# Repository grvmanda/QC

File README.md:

# QC

Attempt at making an all custom hardware quadcop to serve as a platform to test control algorithms

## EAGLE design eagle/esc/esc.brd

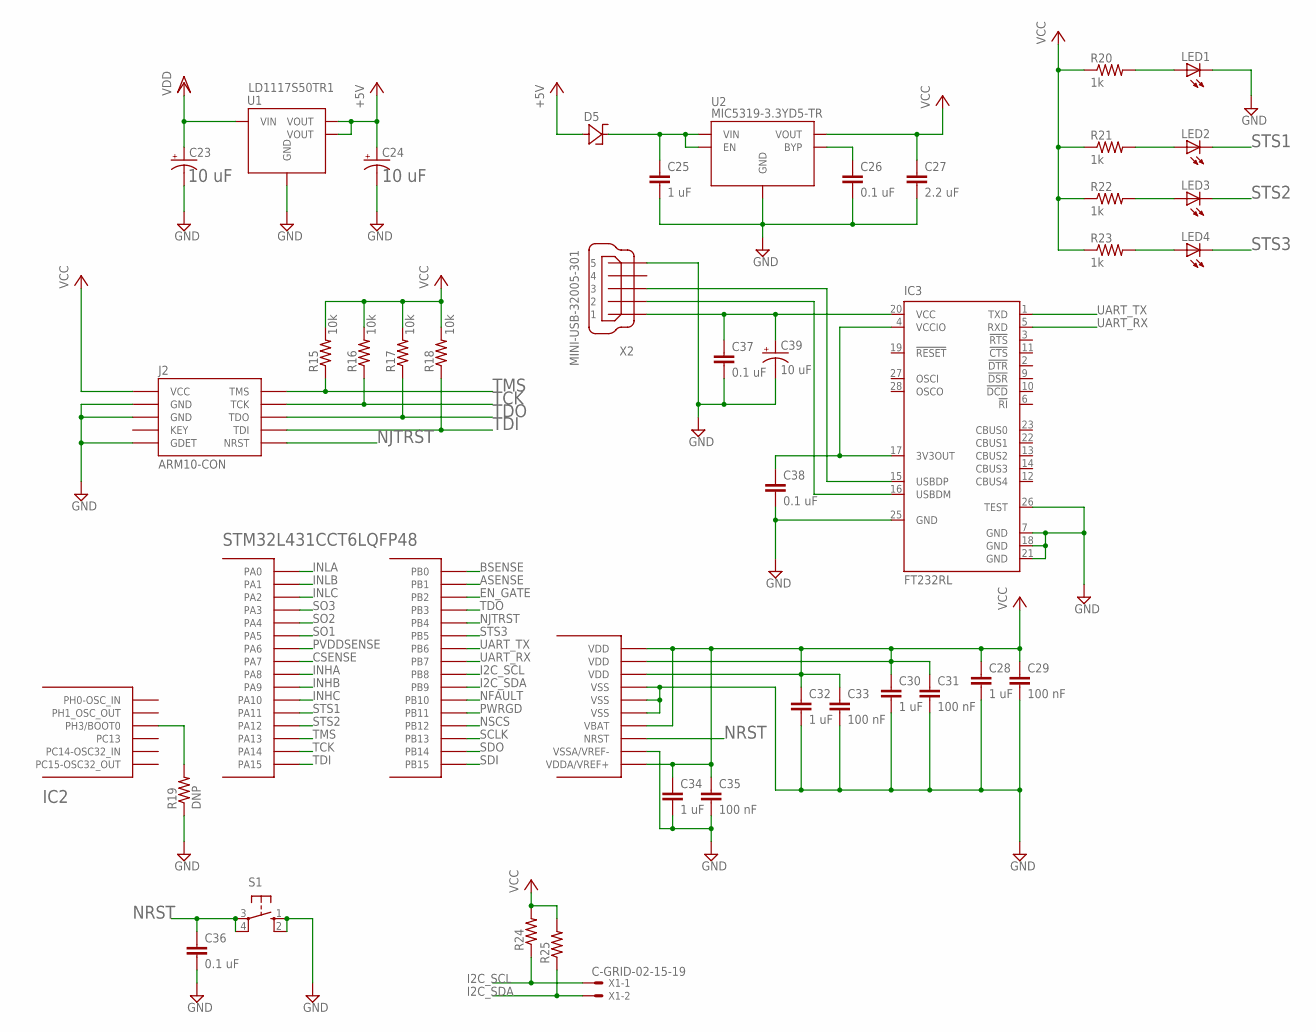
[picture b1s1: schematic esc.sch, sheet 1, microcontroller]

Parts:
C23: 10 uF; CAPAE430X580N
C24: CAPACITOR4.3X4.3; CAPAE430X580N
C25, C28, C30, C32, C34: 1 uF; C0603
C26, C36, C37, C38: 0.1 uF; C0603
C27: 2.2 uF; C0603
C29, C31, C33, C35: 100 nF; C0603
C39: 10 uF; CT3216
D5: STPS2L30ASMA; DIOM5025X245N
IC2: STM32L431CCT6LQFP48; QFP50P900X900X160-48N
IC3: FT232RL; SSOP28
J2: ARM10-CON; 10-PIN-1.27-PITCH
LED1, LED2, LED3, LED4: LED_ESML0603; LED_SML0603
R15, R16, R17, R18: 10k; R0603
R19: DNP; R0603
R20, R21, R22, R23: 1k; R0603
R24, R25: R-US_R0603; R0603
S1: 10-XX; B3F-10XX
U1: LD1117S50TR1; SOT230P700X180-4N
U2: MIC5319-3.3YD5-TR; SOT95P290X110-5N
X1: C-GRID-02-15-19; 15-91-02
X2: MINI-USB-32005-301; 32005-301

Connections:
+5V: C24.1 (+), D5.2 (A), U1.2 (VOUT), U1.4 (VOUT)
ASENSE: IC2.19 (PB1); also elsewhere on the board
BSENSE: IC2.18 (PB0); also elsewhere on the board
CSENSE: IC2.17 (PA7); also elsewhere on the board
EN_GATE: IC2.20 (PB2); also elsewhere on the board
GND: C23.2 (-), C24.2 (-), C25.2, C26.2, C27.2, C28.2, C29.2, C30.2, C31.2, C32.2, C33.2, C34.2, C35.2, C36.2, C37.2, C38.2, C39.+ (-), IC2.8 (VSSA/VREF-), IC2.23 (VSS), IC2.35 (VSS), IC2.47 (VSS), IC3.7 (GND), IC3.18 (GND), IC3.21 (GND), IC3.25 (GND), IC3.26 (TEST), J2.3 (GND), J2.5 (GND), J2.9 (GDET), LED1.C, R19.1, S1.1 (S), S1.2 (S1), U1.1 (GND), U2.2 (GND), X2.5; also elsewhere on the board
I2C_SCL: IC2.45 (PB8), R24.1, X1.1
I2C_SDA: IC2.46 (PB9), R25.1, X1.2
INHA: IC2.29 (PA8); also elsewhere on the board
INHB: IC2.30 (PA9); also elsewhere on the board
INHC: IC2.31 (PA10); also elsewhere on the board
INLA: IC2.10 (PA0); also elsewhere on the board
INLB: IC2.11 (PA1); also elsewhere on the board
INLC: IC2.12 (PA2); also elsewhere on the board
unnamed: C25.1, D5.1 (C), U2.1 (VIN), U2.3 (EN)
unnamed: C26.1, U2.4 (BYP)
unnamed: IC2.44 (PH3/BOOT0), R19.2
unnamed: LED1.A, R20.2
unnamed: C37.1, C39.- (+), IC3.20 (VCC), X2.1
unnamed: LED2.A, R21.2
unnamed: LED3.A, R22.2
unnamed: LED4.A, R23.2
unnamed: C38.1, IC3.4 (VCCIO), IC3.17 (3V3OUT)
unnamed: IC3.16 (USBDM), X2.2
unnamed: IC3.15 (USBDP), X2.3
NFAULT: IC2.21 (PB10); also elsewhere on the board
NJTRST: IC2.40 (PB4), J2.10 (NRST)
NRST: C36.1, IC2.7 (NRST), S1.3, S1.4 (P1)
NSCS: IC2.25 (PB12); also elsewhere on the board
PVDDSENSE: IC2.16 (PA6); also elsewhere on the board
PWRGD: IC2.22 (PB11); also elsewhere on the board
SCLK: IC2.26 (PB13); also elsewhere on the board
SDI: IC2.28 (PB15); also elsewhere on the board
SDO: IC2.27 (PB14); also elsewhere on the board
SO1: IC2.15 (PA5); also elsewhere on the board
SO2: IC2.14 (PA4); also elsewhere on the board
SO3: IC2.13 (PA3); also elsewhere on the board
STS1: IC2.32 (PA11), LED2.C
STS2: IC2.33 (PA12), LED3.C
STS3: IC2.41 (PB5), LED4.C
TCK: IC2.37 (PA14), J2.4 (TCK), R16.1
TDI: IC2.38 (PA15), J2.8 (TDI), R18.1
TDO: IC2.39 (PB3), J2.6 (TDO), R17.1
TMS: IC2.34 (PA13), J2.2 (TMS), R15.1
UART_RX: IC2.43 (PB7), IC3.5 (RXD)
UART_TX: IC2.42 (PB6), IC3.1 (TXD)
VCC: C27.1, C28.1, C29.1, C30.1, C31.1, C32.1, C33.1, C34.1, C35.1, IC2.1 (VBAT), IC2.9 (VDDA/VREF+), IC2.24 (VDD), IC2.36 (VDD), IC2.48 (VDD), J2.1 (VCC), R15.2, R16.2, R17.2, R18.2, R20.1, R21.1, R22.1, R23.1, R24.2, R25.2, U2.5 (VOUT); also elsewhere on the board
VDD: C23.1 (+), U1.3 (VIN); also elsewhere on the board

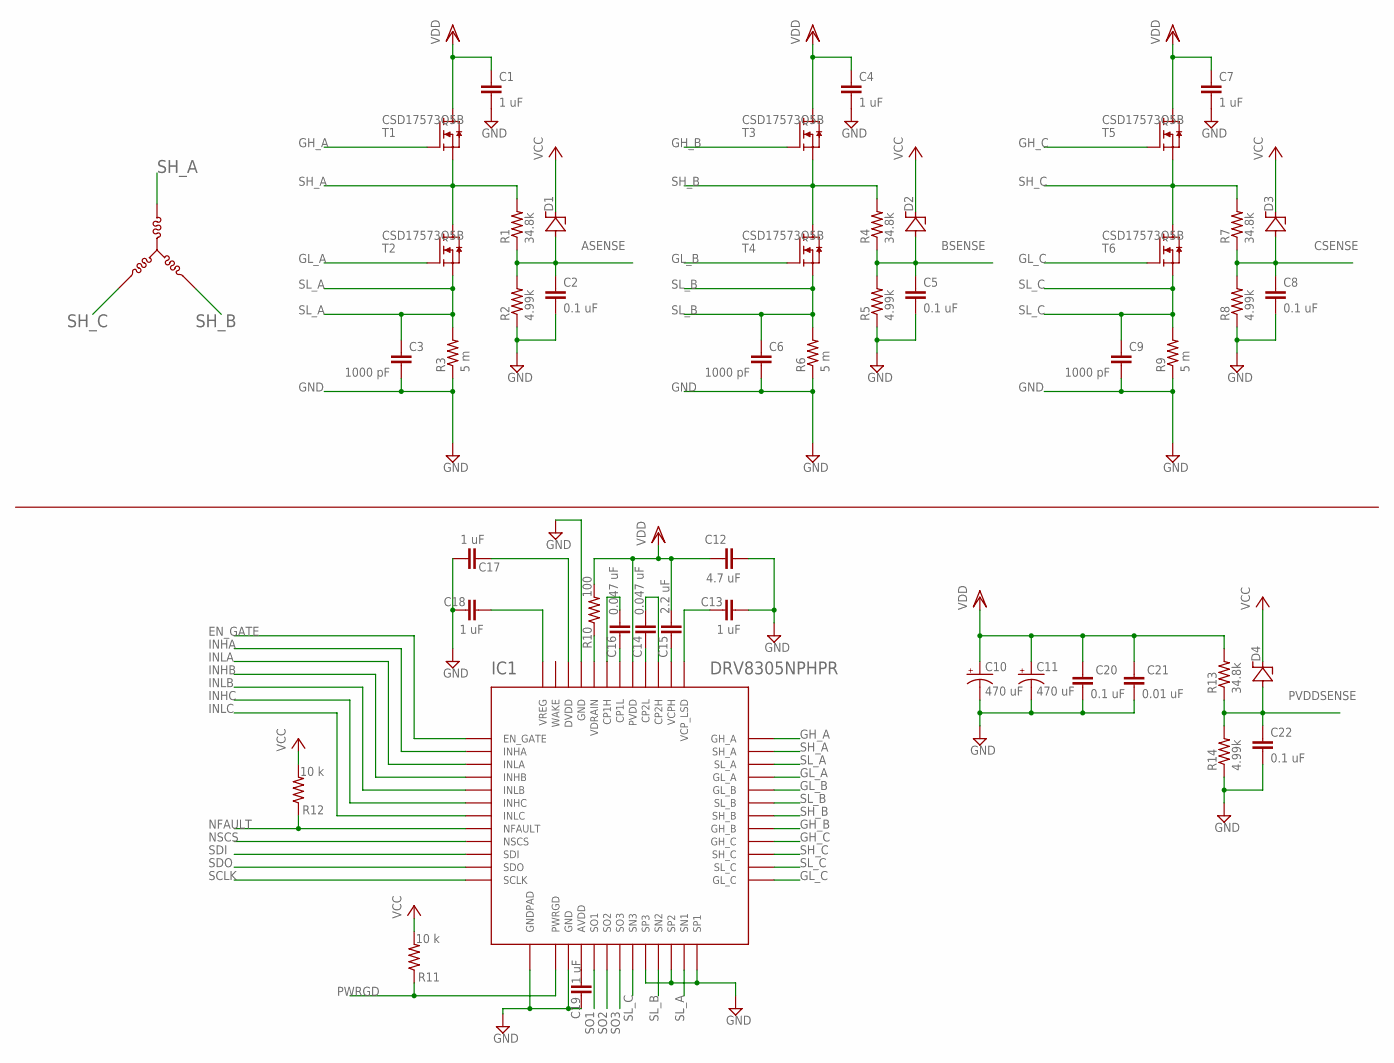
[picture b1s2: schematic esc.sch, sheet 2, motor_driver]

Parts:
C1, C4, C7, C13, C17, C18, C19: 1 uF; C0603
C2, C5, C8: 0.1 uF; C0402
C3, C6, C9: 1000 pF; C0603
C10: 470 uF; E5-10,5
C11: 470 uF; E5-13
C12: 4.7 uF; C0805
C14, C16: 0.047 uF; C0603
C15: 2.2 uF; C0603
C20, C22: 0.1 uF; C0603
C21: 0.01 uF; C0603
D1, D2, D3, D4: STPS2L30ASMA; DIOM5025X245N
IC1: DRV8305NPHPR; 48-HTQFP
R1, R4, R7: 34.8k; R0402
R2, R5, R8: 4.99k; R0402
R3, R6, R9: 5 m; R0603
R10: 100; R0603
R11, R12: 10 k; R0603
R13: 34.8k; R0603
R14: 4.99k; R0603
T1, T2, T3, T4, T5, T6: CSD17573Q5B; 8-POWERTDFN

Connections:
ASENSE: C2.1, D1.2 (A), R1.1, R2.2; also elsewhere on the board
BSENSE: C5.1, D2.2 (A), R4.1, R5.2; also elsewhere on the board
CSENSE: C8.1, D3.2 (A), R7.1, R8.2; also elsewhere on the board
EN_GATE: IC1.1 (EN_GATE); also elsewhere on the board
GH_A: IC1.36 (GH_A), T1.4 (G)
GH_B: IC1.29 (GH_B), T3.4 (G)
GH_C: IC1.28 (GH_C), T5.4 (G)
GL_A: IC1.33 (GL_A), T2.4 (G)
GL_B: IC1.32 (GL_B), T4.4 (G)
GL_C: IC1.25 (GL_C), T6.4 (G)
GND: C1.2, C2.2, C3.2, C4.2, C5.2, C6.2, C7.2, C8.2, C9.2, C10.-, C11.-, C12.2, C13.2, C17.2, C18.1, C19.1, C20.1, C21.1, C22.2, IC1.14 (GND), IC1.20 (SP3), IC1.22 (SP2), IC1.24 (SP1), IC1.45 (GND), IC1.49 (GNDPAD), R2.1, R3.1, R5.1, R6.1, R8.1, R9.1, R14.1; also elsewhere on the board
INHA: IC1.2 (INHA); also elsewhere on the board
INHB: IC1.4 (INHB); also elsewhere on the board
INHC: IC1.6 (INHC); also elsewhere on the board
INLA: IC1.3 (INLA); also elsewhere on the board
INLB: IC1.5 (INLB); also elsewhere on the board
INLC: IC1.7 (INLC); also elsewhere on the board
unnamed: C13.1, IC1.37 (VCP_LSD)
unnamed: C16.1, IC1.42 (CP1L)
unnamed: C14.2, IC1.39 (CP2H)
unnamed: C14.1, IC1.40 (CP2L)
unnamed: C15.1, IC1.38 (VCPH)
unnamed: C16.2, IC1.43 (CP1H)
unnamed: C18.2, IC1.48 (VREG)
unnamed: IC1.44 (VDRAIN), R10.1
unnamed: C17.1, IC1.46 (DVDD)
unnamed: C19.2, IC1.15 (AVDD)
NFAULT: IC1.8 (NFAULT), R12.1; also elsewhere on the board
NSCS: IC1.9 (NSCS); also elsewhere on the board
PVDDSENSE: C22.1, D4.2 (A), R13.1, R14.2; also elsewhere on the board
PWRGD: IC1.13 (PWRGD), R11.1; also elsewhere on the board
SCLK: IC1.12 (SCLK); also elsewhere on the board
SDI: IC1.10 (SDI); also elsewhere on the board
SDO: IC1.11 (SDO); also elsewhere on the board
SH_A: IC1.35 (SH_A), R1.2, T1.1 (S), T1.2 (S), T1.3 (S), T2.5 (D)
SH_B: IC1.30 (SH_B), R4.2, T3.1 (S), T3.2 (S), T3.3 (S), T4.5 (D)
SH_C: IC1.27 (SH_C), R7.2, T5.1 (S), T5.2 (S), T5.3 (S), T6.5 (D)
SL_A: C3.1, IC1.23 (SN1), IC1.34 (SL_A), R3.2, T2.1 (S), T2.2 (S), T2.3 (S)
SL_B: C6.1, IC1.21 (SN2), IC1.31 (SL_B), R6.2, T4.1 (S), T4.2 (S), T4.3 (S)
SL_C: C9.1, IC1.19 (SN3), IC1.26 (SL_C), R9.2, T6.1 (S), T6.2 (S), T6.3 (S)
SO1: IC1.16 (SO1); also elsewhere on the board
SO2: IC1.17 (SO2); also elsewhere on the board
SO3: IC1.18 (SO3); also elsewhere on the board
VCC: D1.1 (C), D2.1 (C), D3.1 (C), D4.1 (C), R11.2, R12.2; also elsewhere on the board
VDD: C1.1, C4.1, C7.1, C10.+, C11.+, C12.1, C15.2, C20.2, C21.2, IC1.41 (PVDD), R10.2, R13.2, T1.5 (D), T3.5 (D), T5.5 (D); also elsewhere on the board

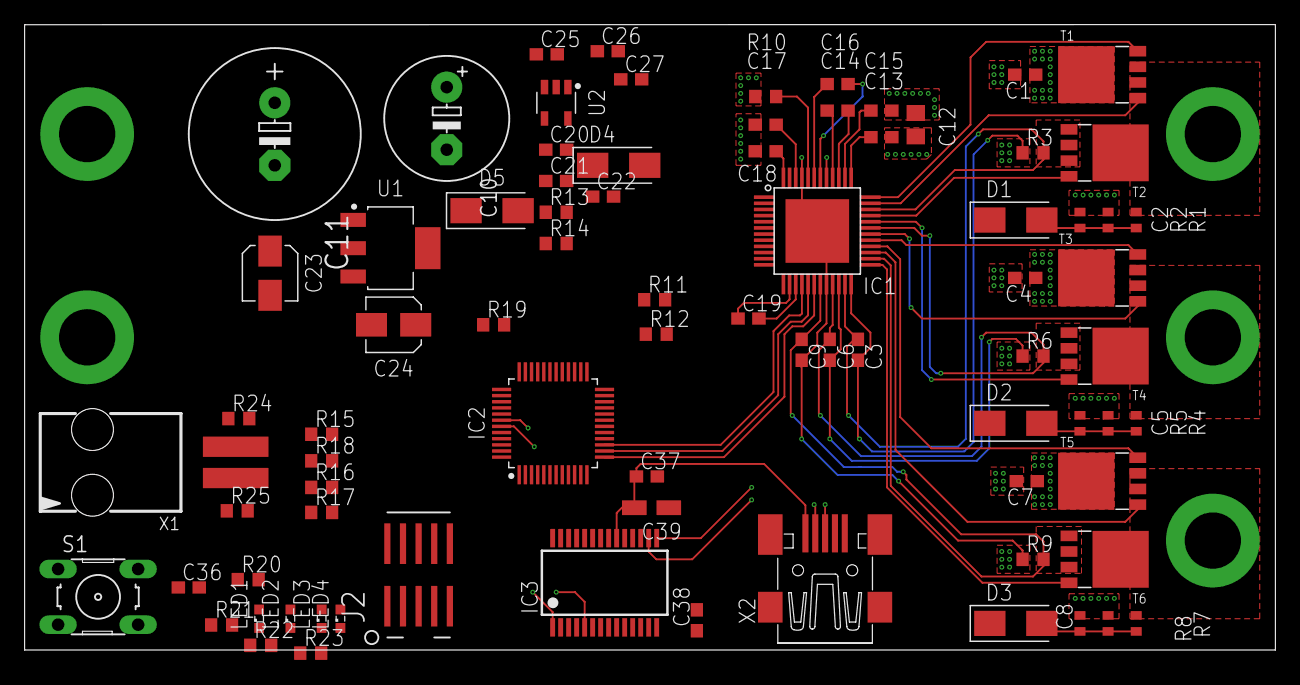
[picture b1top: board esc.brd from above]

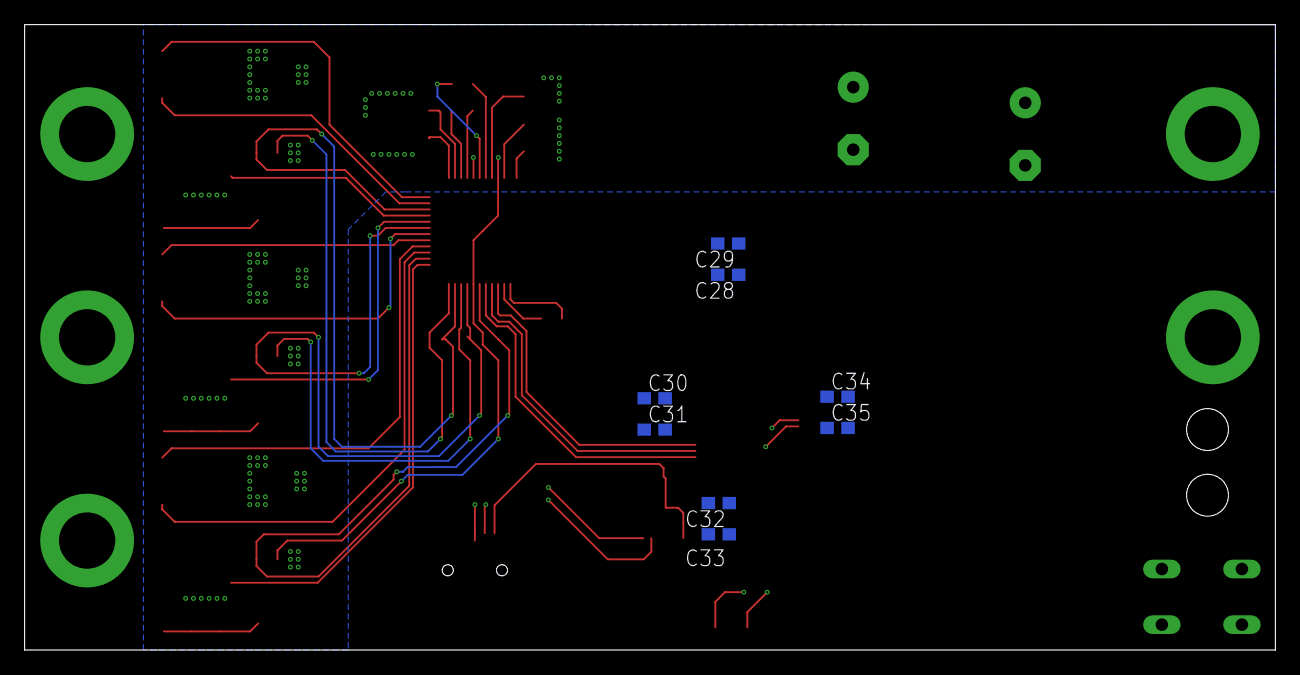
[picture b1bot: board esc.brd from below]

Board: 4 copper layers, 101.6 x 50.8 mm, 88 parts (8 on the bottom side), 70 nets.

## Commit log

2020-01-06 preliminary frame designs
2020-01-10 updated ESC board schematic, added bom, some papers as well
2020-03-11 added FETs and related circuitry for the motor drive, current sense
2020-03-11 adding gitignore
2020-03-18 testing git on RPi
2020-04-04 Added most of the components to the schematic. Left to add connectors for SPI port for micro and power connectors
2020-04-05 added pinMapping spreadsheet for ESC. this is up-to-date with the pinout mapping for the micro
2020-04-05 updated pinMapping with Port Names
2020-04-05 completed schematic of esc
2020-04-06 Board layout save 1. Completed driver layout
2020-05-12 updated pin mappings - changed a bunch for better placements
